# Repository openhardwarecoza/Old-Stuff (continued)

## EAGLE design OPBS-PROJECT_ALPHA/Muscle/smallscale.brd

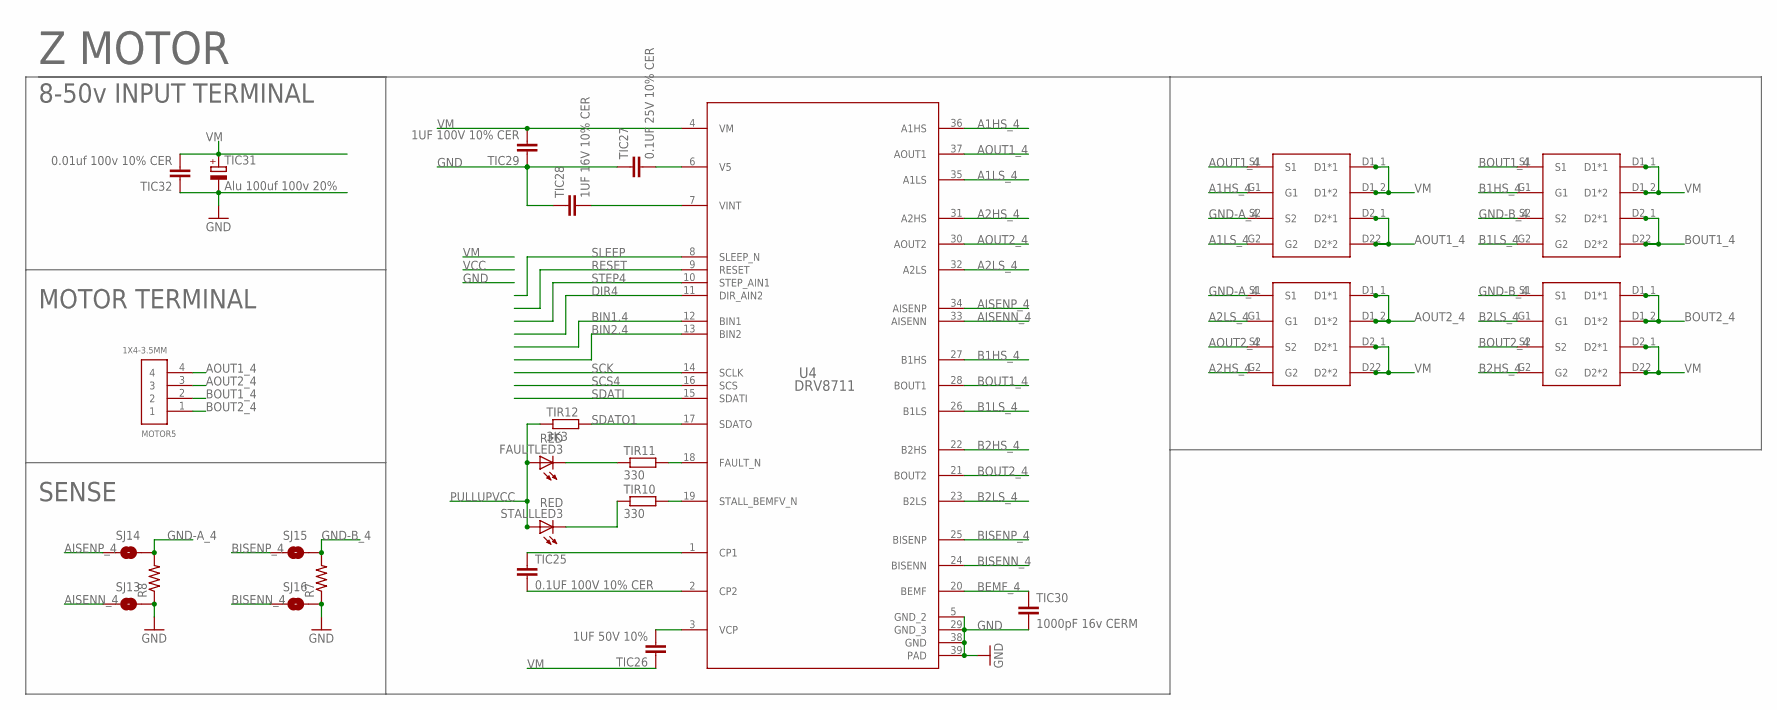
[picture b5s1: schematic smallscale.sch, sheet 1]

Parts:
FAULTLED3: RED; 1206
MOTOR5: 1X4-3.5MM; 1X04-3.5MM
R7, R8: R-US_R2512; R2512
SJ13, SJ14, SJ15, SJ16: SOLDERJUMPERTRACE; SJ_2S-TRACE
STALLLED3: RED; 1206
TIC25: 0.1UF 100V 10% CER; C0603K
TIC26: 1UF 50V 10%; C0805K
TIC27: 0.1UF 25V 10% CER; C0603K
TIC28: 1UF 16V 10% CER; C0603K
TIC29: 1UF 100V 10% CER; C1206K
TIC30: 1000pF 16v CERM; C0603K
TIC31: Alu 100uf 100v 20%; E5-10,5
TIC32: 0.01uf 100v 10% CER; C0603K
TIR10, TIR11: 330; R1206
TIR12: 3K3; R1206
U4: DRV8711; DCP0038A_N
U$13, U$14, U$15, U$16: CSD88537ND

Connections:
A1HS_4: U4.36 (A1HS), U$13.G1
A1LS_4: U4.35 (A1LS), U$13.G2
A2HS_4: U4.31 (A2HS), U$15.G2
A2LS_4: U4.32 (A2LS), U$15.G1
AISENN_4: SJ13.1, U4.33 (AISENN)
AISENP_4: SJ14.1, U4.34 (AISENP)
AOUT1_4: MOTOR5.4, U4.37 (AOUT1), U$13.D2_1 (D2*1), U$13.D22 (D2*2), U$13.S1
AOUT2_4: MOTOR5.3, U4.30 (AOUT2), U$15.D1_1 (D1*1), U$15.D1_2 (D1*2), U$15.S2
B1HS_4: U4.27 (B1HS), U$14.G1
B1LS_4: U4.26 (B1LS), U$14.G2
B2HS_4: U4.22 (B2HS), U$16.G2
B2LS_4: U4.23 (B2LS), U$16.G1
BEMF_4: TIC30.1, U4.20 (BEMF)
BIN1.4: U4.12 (BIN1)
BIN2.4: U4.13 (BIN2)
BISENN_4: SJ16.1, U4.24 (BISENN)
BISENP_4: SJ15.1, U4.25 (BISENP)
BOUT1_4: MOTOR5.2, U4.28 (BOUT1), U$14.D2_1 (D2*1), U$14.D22 (D2*2), U$14.S1
BOUT2_4: MOTOR5.1, U4.21 (BOUT2), U$16.D1_1 (D1*1), U$16.D1_2 (D1*2), U$16.S2
CP1_4: TIC25.1, U4.1 (CP1)
CP2_4: TIC25.2, U4.2 (CP2)
DIR4: U4.11 (DIR_AIN2)
FAULTLED4: FAULTLED3.C, TIR11.1
FAULT_N4: TIR11.2, U4.18 (FAULT_N)
GND: R7.1, R8.1, SJ13.2, SJ16.2, TIC27.1, TIC28.1, TIC29.1, TIC30.2, TIC31.-, TIC32.1, U4.5 (GND_2), U4.29 (GND_3), U4.38 (GND), U4.39 (PAD); also elsewhere on the board
GND-A_4: R8.2, SJ14.2, U$13.S2, U$15.S1
GND-B_4: R7.2, SJ15.2, U$14.S2, U$16.S1
PULLUPVCC: FAULTLED3.A, STALLLED3.A, TIR12.1
RESET: U4.9 (RESET)
SCK: U4.14 (SCLK)
SCS4: U4.16 (SCS)
SDATI: U4.15 (SDATI)
SDATO1: TIR12.2, U4.17 (SDATO)
SLEEP: U4.8 (SLEEP_N)
STALLLED4: STALLLED3.C, TIR10.1
STALL_N4: TIR10.2, U4.19 (STALL_BEMFV_N)
STEP4: U4.10 (STEP_AIN1)
V5_4: TIC27.2, U4.6 (V5)
VCP4: TIC26.2, U4.3 (VCP)
VINT4: TIC28.2, U4.7 (VINT)
VM: TIC26.1, TIC29.2, TIC31.+, TIC32.2, U4.4 (VM), U$13.D1_1 (D1*1), U$13.D1_2 (D1*2), U$14.D1_1 (D1*1), U$14.D1_2 (D1*2), U$15.D2_1 (D2*1), U$15.D22 (D2*2), U$16.D2_1 (D2*1), U$16.D22 (D2*2); also elsewhere on the board

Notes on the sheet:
8-50v INPUT TERMINAL
MOTOR TERMINAL
SENSE
Z MOTOR

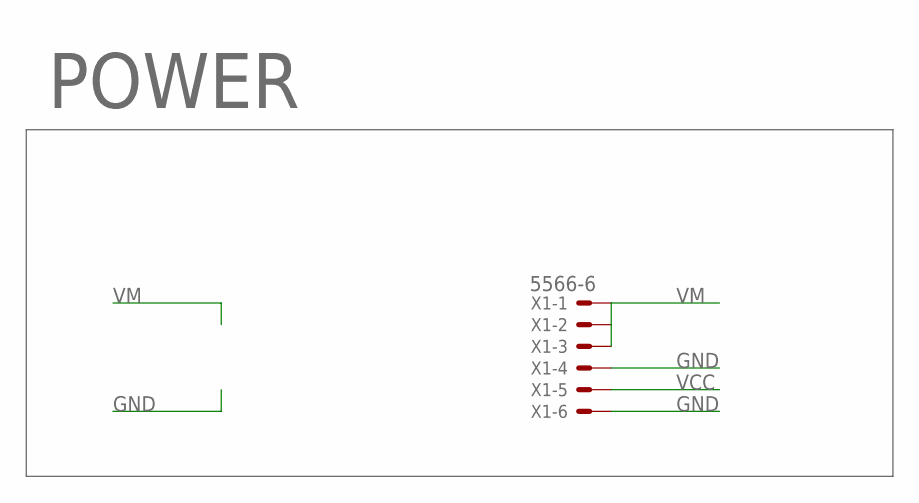
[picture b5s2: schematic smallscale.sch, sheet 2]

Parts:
X1: 5566-6

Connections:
GND: X1.4, X1.6; also elsewhere on the board
VCC: X1.5
VM: X1.1, X1.2, X1.3; also elsewhere on the board

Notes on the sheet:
POWER

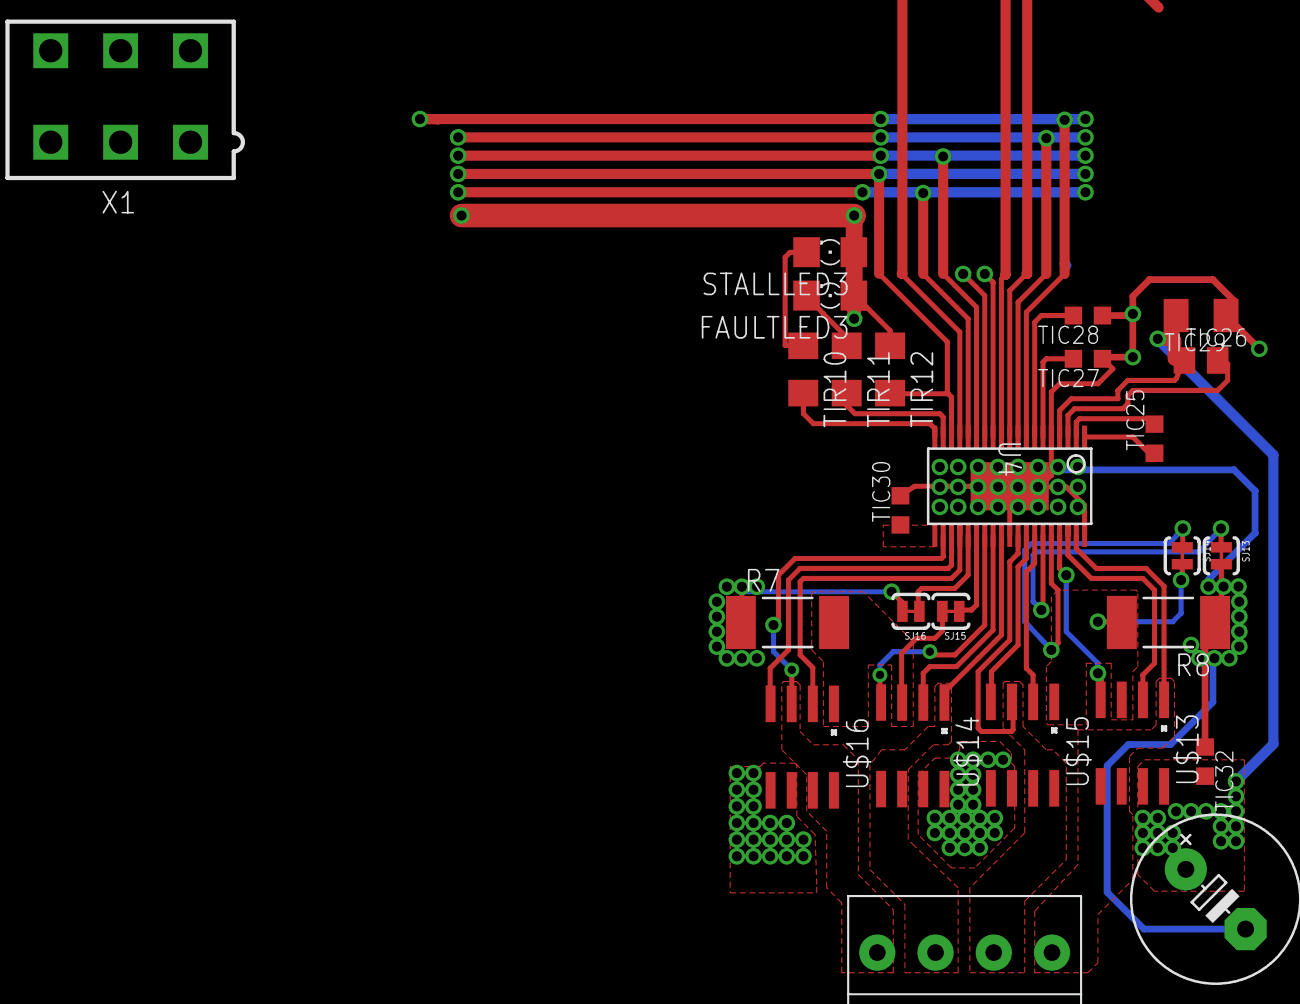
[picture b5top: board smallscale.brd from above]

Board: 2 copper layers, 26 parts (0 on the bottom side), 32 nets.

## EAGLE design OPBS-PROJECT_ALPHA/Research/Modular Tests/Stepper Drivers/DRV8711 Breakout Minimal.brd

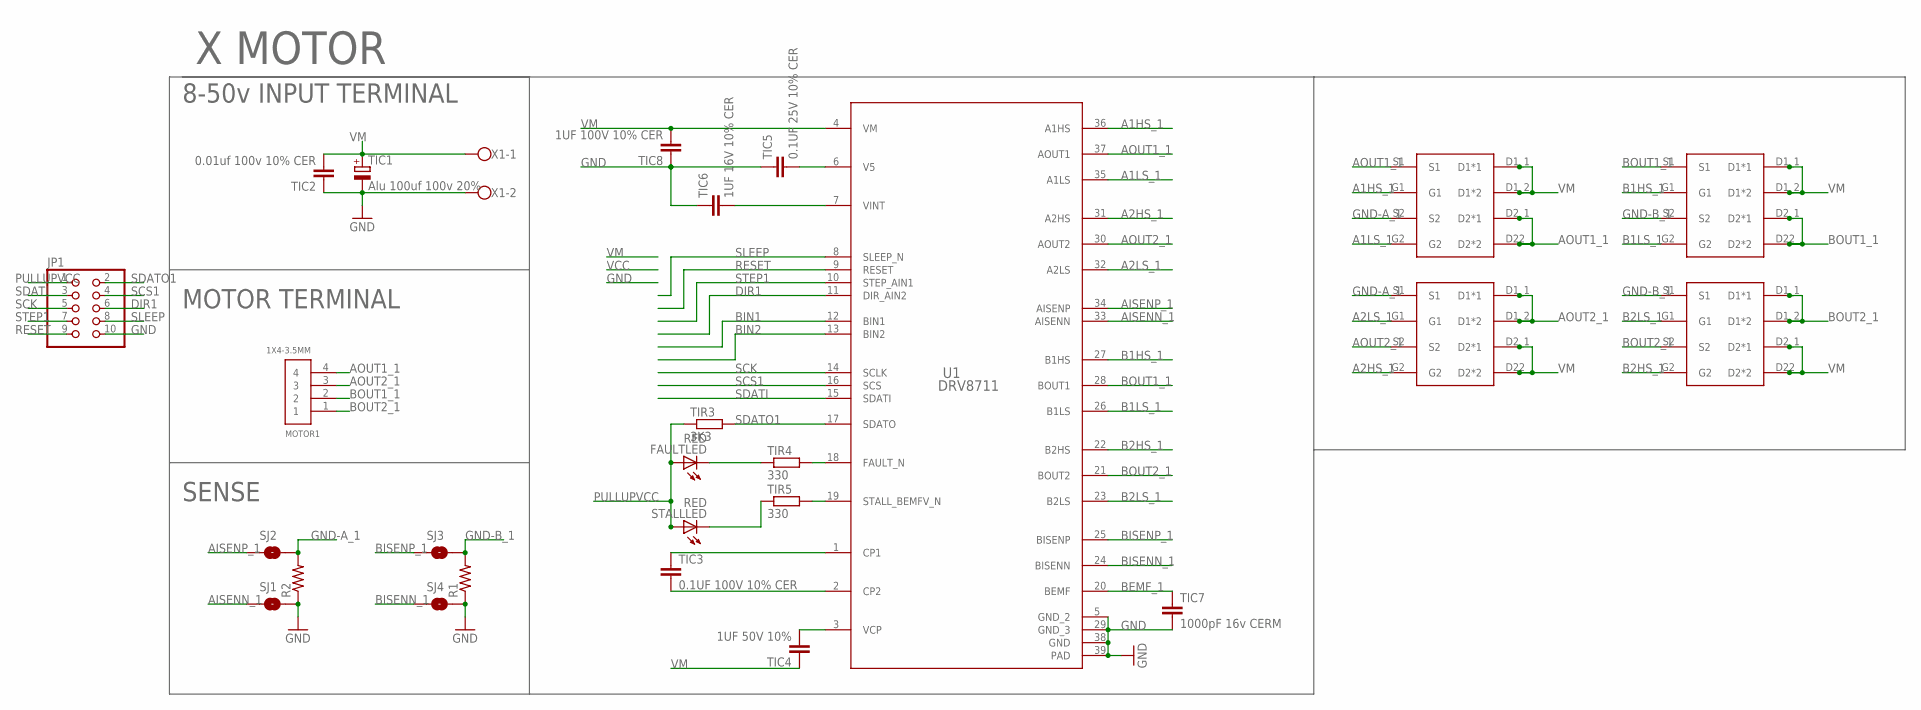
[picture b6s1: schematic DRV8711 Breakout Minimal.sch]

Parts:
FAULTLED: RED; 1206
JP1: PINHD-2X5; 2X05
MOTOR1: 1X4-3.5MM; 1X04-3.5MM
R1, R2: R-US_R2512; R2512
SJ1, SJ2, SJ3, SJ4: SOLDERJUMPERTRACE; SJ_2S-TRACE
STALLLED: RED; 1206
TIC1: Alu 100uf 100v 20%; PANASONIC_E
TIC2: 0.01uf 100v 10% CER; C1206K
TIC3: 0.1UF 100V 10% CER; C1206K
TIC4: 1UF 50V 10%; C1206K
TIC5: 0.1UF 25V 10% CER; C1206K
TIC6: 1UF 16V 10% CER; C1206K
TIC7: 1000pF 16v CERM; C1206K
TIC8: 1UF 100V 10% CER; C1206K
TIR3: 3K3; R1206
TIR4, TIR5: 330; R1206
U1: DRV8711; DCP0038A_N
U$1, U$2, U$3, U$4: CSD88537ND
X1: W237-102

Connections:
A1HS_1: U1.36 (A1HS), U$1.G1
A1LS_1: U1.35 (A1LS), U$1.G2
A2HS_1: U1.31 (A2HS), U$3.G2
A2LS_1: U1.32 (A2LS), U$3.G1
AISENN_1: SJ1.1, U1.33 (AISENN)
AISENP_1: SJ2.1, U1.34 (AISENP)
AOUT1_1: MOTOR1.4, U1.37 (AOUT1), U$1.D2_1 (D2*1), U$1.D22 (D2*2), U$1.S1
AOUT2_1: MOTOR1.3, U1.30 (AOUT2), U$3.D1_1 (D1*1), U$3.D1_2 (D1*2), U$3.S2
B1HS_1: U1.27 (B1HS), U$2.G1
B1LS_1: U1.26 (B1LS), U$2.G2
B2HS_1: U1.22 (B2HS), U$4.G2
B2LS_1: U1.23 (B2LS), U$4.G1
BEMF_1: TIC7.1, U1.20 (BEMF)
BIN1: U1.12 (BIN1)
BIN2: U1.13 (BIN2)
BISENN_1: SJ4.1, U1.24 (BISENN)
BISENP_1: SJ3.1, U1.25 (BISENP)
BOUT1_1: MOTOR1.2, U1.28 (BOUT1), U$2.D2_1 (D2*1), U$2.D22 (D2*2), U$2.S1
BOUT2_1: MOTOR1.1, U1.21 (BOUT2), U$4.D1_1 (D1*1), U$4.D1_2 (D1*2), U$4.S2
CP1_1: TIC3.1, U1.1 (CP1)
CP2_1: TIC3.2, U1.2 (CP2)
DIR1: JP1.6, U1.11 (DIR_AIN2)
FAULTLED: FAULTLED.C, TIR4.1
FAULT_N1: TIR4.2, U1.18 (FAULT_N)
GND: JP1.10, R1.1, R2.1, SJ1.2, SJ4.2, TIC1.-, TIC2.1, TIC5.1, TIC6.1, TIC7.2, TIC8.1, U1.5 (GND_2), U1.29 (GND_3), U1.38 (GND), U1.39 (PAD), X1.2
GND-A_1: R2.2, SJ2.2, U$1.S2, U$3.S1
GND-B_1: R1.2, SJ3.2, U$2.S2, U$4.S1
PULLUPVCC: FAULTLED.A, JP1.1, STALLLED.A, TIR3.1
RESET: JP1.9, U1.9 (RESET)
SCK: JP1.5, U1.14 (SCLK)
SCS1: JP1.4, U1.16 (SCS)
SDATI: JP1.3, U1.15 (SDATI)
SDATO1: JP1.2, TIR3.2, U1.17 (SDATO)
SLEEP: JP1.8, U1.8 (SLEEP_N)
STALLLED: STALLLED.C, TIR5.1
STALL_N1: TIR5.2, U1.19 (STALL_BEMFV_N)
STEP1: JP1.7, U1.10 (STEP_AIN1)
V5_1: TIC5.2, U1.6 (V5)
VCP1: TIC4.2, U1.3 (VCP)
VINT1: TIC6.2, U1.7 (VINT)
VM: TIC1.+, TIC2.2, TIC4.1, TIC8.2, U1.4 (VM), U$1.D1_1 (D1*1), U$1.D1_2 (D1*2), U$2.D1_1 (D1*1), U$2.D1_2 (D1*2), U$3.D2_1 (D2*1), U$3.D22 (D2*2), U$4.D2_1 (D2*1), U$4.D22 (D2*2), X1.1

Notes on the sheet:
8-50v INPUT TERMINAL
MOTOR TERMINAL
SENSE
X MOTOR

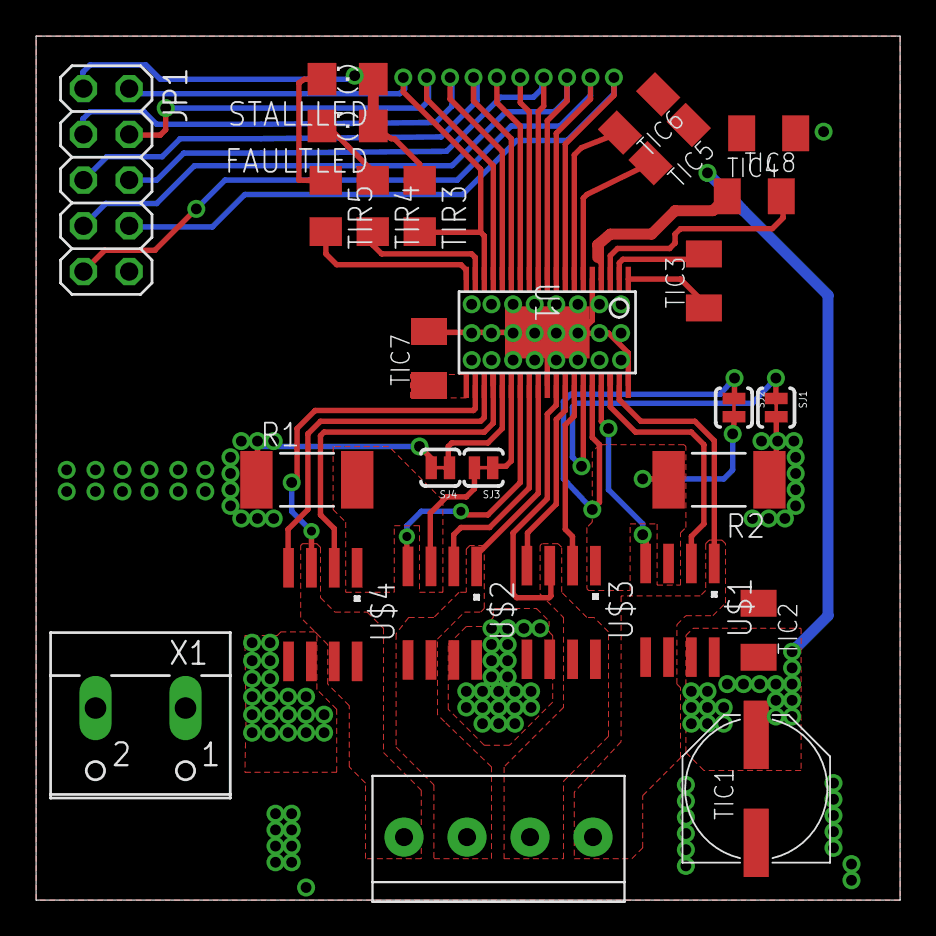
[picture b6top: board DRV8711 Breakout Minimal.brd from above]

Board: 2 copper layers, 48.0 x 48.0 mm, 27 parts (0 on the bottom side), 39 nets.

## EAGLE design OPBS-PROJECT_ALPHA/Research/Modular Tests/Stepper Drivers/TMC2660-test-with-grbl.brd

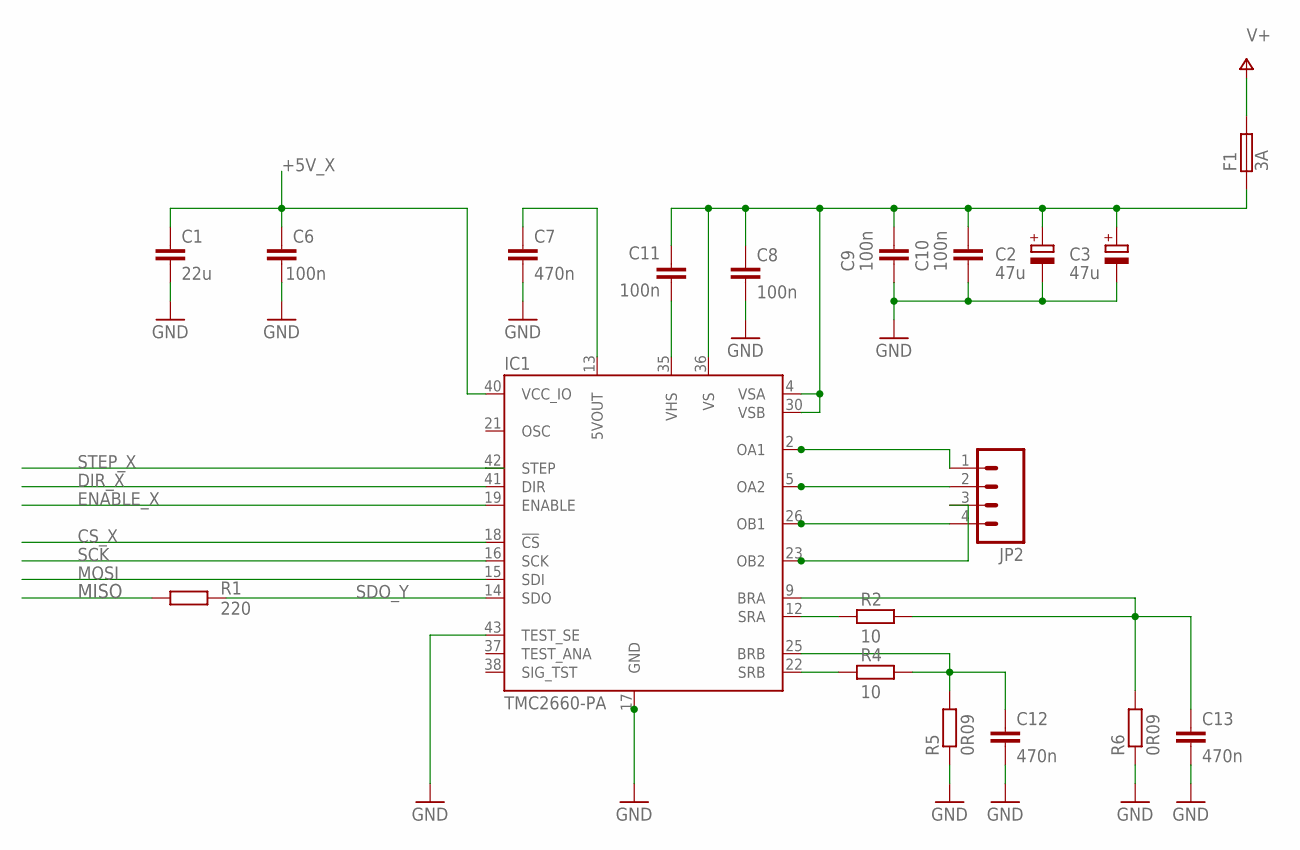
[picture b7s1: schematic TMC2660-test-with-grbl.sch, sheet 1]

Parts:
C1: 22u; C1206; VOLTAGE 6.3V; PARTNR JMK316B7226ML-T
C2, C3: 47u; E5-8,5; VOLTAGE 50V; PARTNR EEEFK1H470XP
C6: 100n; C1206K; VOLTAGE 25V; PARTNR C0603C104K3RACTU
C7, C12, C13: 470n; 0805-WIDE; VOLTAGE 10V; PARTNR VJ0805Y474KXQTW1BC
C8, C9, C10, C11: 100n; C0603K; VOLTAGE 50V; PARTNR C0603C104K5RACTU
F1: 3A; AF2; VOLTAGE 125V; PARTNR CB61F3A-TR2
IC1: TMC2660-PA; PQFP44; PARTNR TMC2660
JP2: M04SCREW; SCREWTERMINAL-3.5MM-4
R1: 220; R0603; PARTNR SG73S1JTTD221J
R2, R4: 10; R0603; PARTNR RN73H1JTTD10R0F100
R5, R6: 0R09; R2512; PARTNR ERJ-B2CFR091V

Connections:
+5V_X: C1.1, C6.2, IC1.40 (VCC_IO)
CS_X: IC1.18 (!CS); also elsewhere on the board
DIR_X: IC1.41 (DIR); also elsewhere on the board
ENABLE_X: IC1.19 (ENABLE); also elsewhere on the board
GND: C1.2, C2.-, C3.-, C6.1, C7.2, C8.2, C9.1, C10.1, C12.2, C13.2, IC1.17 (GND), IC1.39 (GND1), IC1.43 (TEST_SE), IC1.44 (GND2), R5.1, R6.1; also elsewhere on the board
MISO: R1.2; also elsewhere on the board
MOSI: IC1.15 (SDI); also elsewhere on the board
unnamed: IC1.22 (SRB), R4.2
unnamed: C12.1, IC1.25 (BRB), R4.1, R5.2
unnamed: C13.1, IC1.9 (BRA), R2.1, R6.2
unnamed: IC1.12 (SRA), R2.2
OA1: IC1.2 (OA1), IC1.3 (OA1_1), IC1.7 (OA1_2), IC1.8 (OA1_3), JP2.1
OA2: IC1.5 (OA2), IC1.6 (OA2_1), IC1.10 (OA2_2), IC1.11 (OA2_3), JP2.2
OB1: IC1.26 (OB1), IC1.27 (OB1_1), IC1.31 (OB1_2), IC1.32 (OB1_3), JP2.4
OB2: IC1.23 (OB2), IC1.24 (OB2_1), IC1.28 (OB2_2), IC1.29 (OB2_3), JP2.3
PWR_X: C2.+, C3.+, C8.1, C9.2, C10.2, C11.2, F1.P$1 (1), IC1.4 (VSA), IC1.30 (VSB), IC1.36 (VS)
SCK: IC1.16 (SCK); also elsewhere on the board
SDO_Y: IC1.14 (SDO), R1.1
STEP_X: IC1.42 (STEP); also elsewhere on the board
V+: F1.P$2 (2); also elsewhere on the board
VHS: C11.1, IC1.35 (VHS)
VREG: C7.1, IC1.13 (5VOUT)

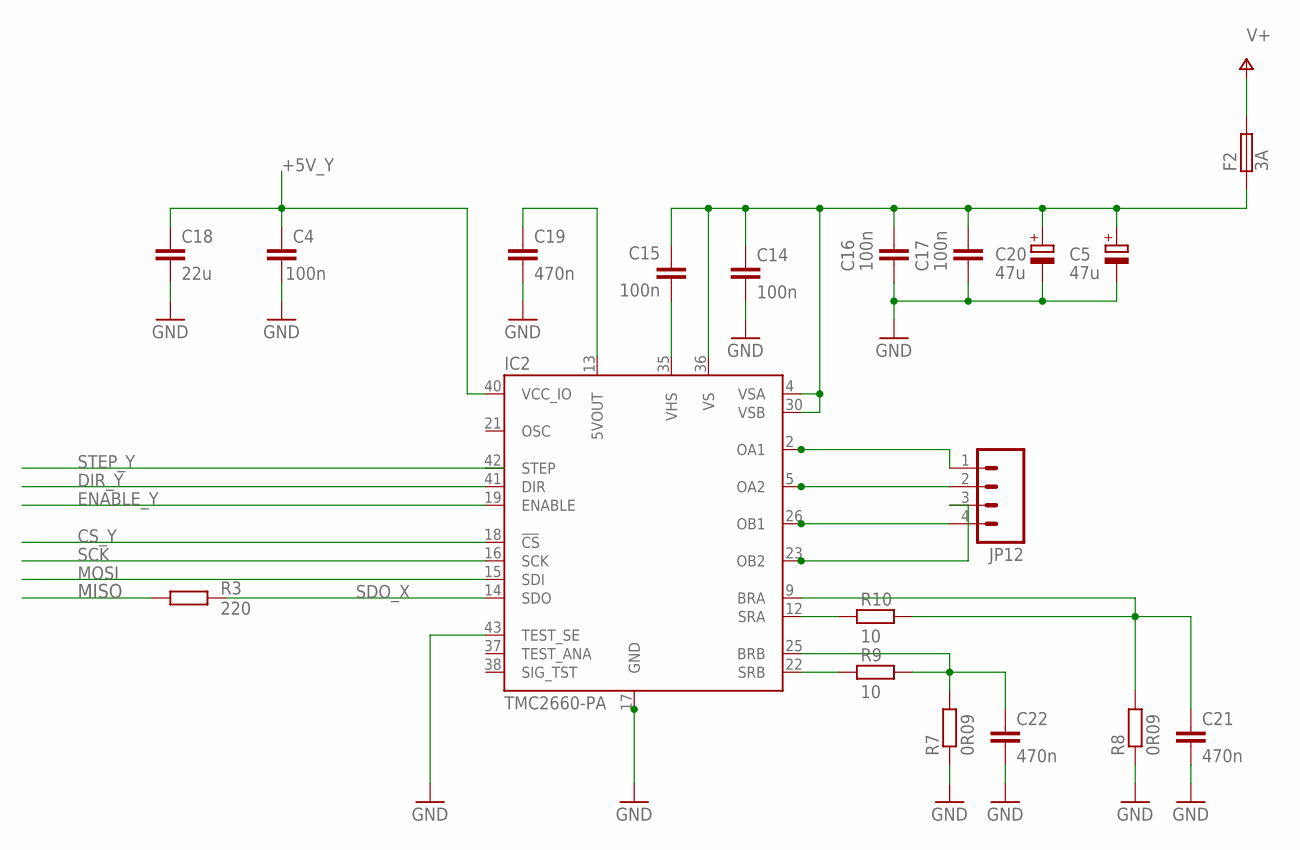
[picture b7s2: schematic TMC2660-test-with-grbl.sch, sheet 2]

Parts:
C4: 100n; C1206K; VOLTAGE 25V; PARTNR C0603C104K3RACTU
C5, C20: 47u; E5-8,5; VOLTAGE 50V; PARTNR EEEFK1H470XP
C14, C15, C16, C17: 100n; C0603K; VOLTAGE 50V; PARTNR C0603C104K5RACTU
C18: 22u; C1206; VOLTAGE 6.3V; PARTNR JMK316B7226ML-T
C19, C21, C22: 470n; 0805-WIDE; VOLTAGE 10V; PARTNR VJ0805Y474KXQTW1BC
F2: 3A; AF2; VOLTAGE 125V; PARTNR CB61F3A-TR2
IC2: TMC2660-PA; PQFP44; PARTNR TMC2660
JP12: M04SCREW; SCREWTERMINAL-3.5MM-4
R3: 220; R0603; PARTNR SG73S1JTTD221J
R7, R8: 0R09; R2512; PARTNR ERJ-B2CFR091V
R9, R10: 10; R0603; PARTNR RN73H1JTTD10R0F100

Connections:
+5V_Y: C4.2, C18.1, IC2.40 (VCC_IO)
CS_Y: IC2.18 (!CS); also elsewhere on the board
DIR_Y: IC2.41 (DIR); also elsewhere on the board
ENABLE_Y: IC2.19 (ENABLE); also elsewhere on the board
GND: C4.1, C5.-, C14.2, C16.1, C17.1, C18.2, C19.2, C20.-, C21.2, C22.2, IC2.17 (GND), IC2.39 (GND1), IC2.43 (TEST_SE), IC2.44 (GND2), R7.1, R8.1; also elsewhere on the board
MISO: R3.2; also elsewhere on the board
MOSI: IC2.15 (SDI); also elsewhere on the board
unnamed: C22.1, IC2.25 (BRB), R7.2, R9.1
unnamed: C21.1, IC2.9 (BRA), R8.2, R10.1
unnamed: IC2.22 (SRB), R9.2
unnamed: IC2.12 (SRA), R10.2
OA3: IC2.2 (OA1), IC2.3 (OA1_1), IC2.7 (OA1_2), IC2.8 (OA1_3), JP12.1
OA4: IC2.5 (OA2), IC2.6 (OA2_1), IC2.10 (OA2_2), IC2.11 (OA2_3), JP12.2
OB3: IC2.23 (OB2), IC2.24 (OB2_1), IC2.28 (OB2_2), IC2.29 (OB2_3), JP12.3
OB4: IC2.26 (OB1), IC2.27 (OB1_1), IC2.31 (OB1_2), IC2.32 (OB1_3), JP12.4
PWR_Y: C5.+, C14.1, C15.2, C16.2, C17.2, C20.+, F2.P$1 (1), IC2.4 (VSA), IC2.30 (VSB), IC2.36 (VS)
SCK: IC2.16 (SCK); also elsewhere on the board
SDO_X: IC2.14 (SDO), R3.1
STEP_Y: IC2.42 (STEP); also elsewhere on the board
V+: F2.P$2 (2); also elsewhere on the board
VHS1: C15.1, IC2.35 (VHS)
VREG1: C19.1, IC2.13 (5VOUT)

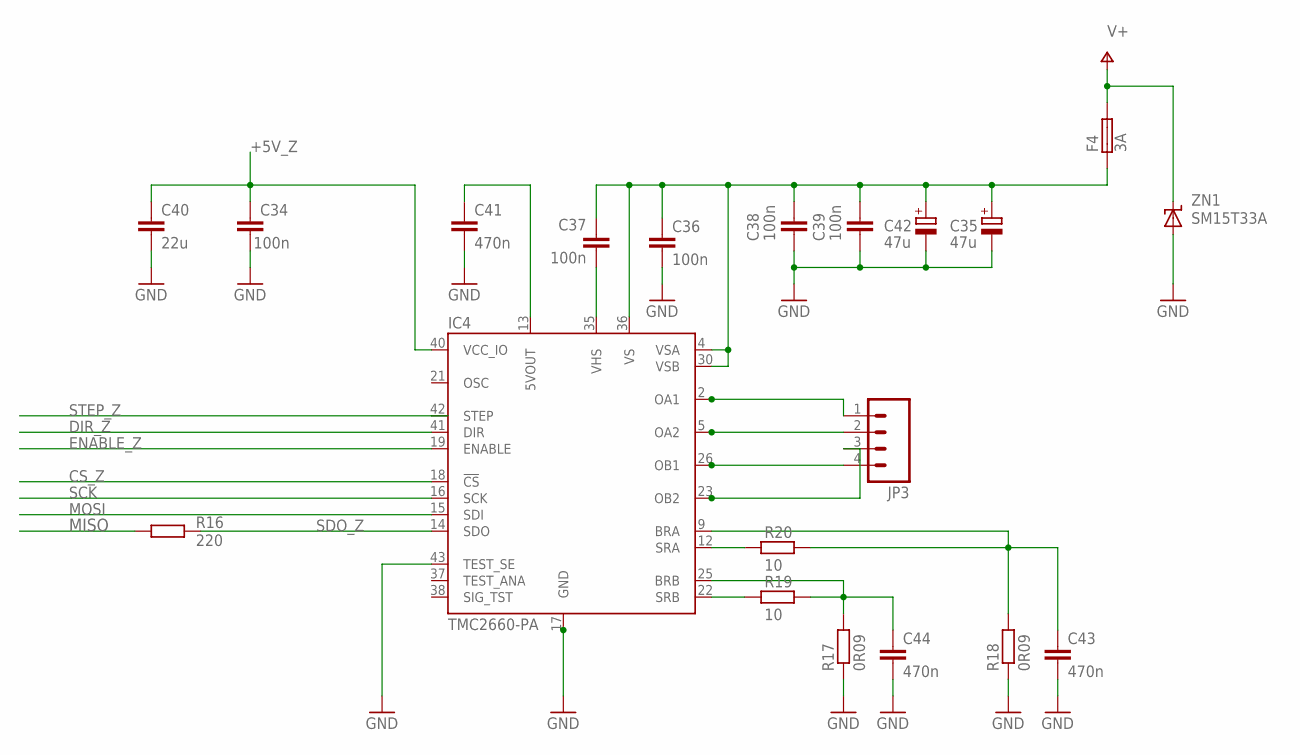
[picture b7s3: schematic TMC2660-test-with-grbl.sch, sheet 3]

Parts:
C34: 100n; C1206K; VOLTAGE 25V; PARTNR C0603C104K3RACTU
C35, C42: 47u; E5-8,5; VOLTAGE 50V; PARTNR EEEFK1H470XP
C36, C37, C38, C39: 100n; C0603K; VOLTAGE 50V; PARTNR C0603C104K5RACTU
C40: 22u; C1206; VOLTAGE 6.3V; PARTNR JMK316B7226ML-T
C41, C43, C44: 470n; 0805-WIDE; VOLTAGE 10V; PARTNR VJ0805Y474KXQTW1BC
F4: 3A; AF2; VOLTAGE 125V; PARTNR CB61F3A-TR2
IC4: TMC2660-PA; PQFP44; PARTNR TMC2660
JP3: M04SCREW; SCREWTERMINAL-3.5MM-4
R16: 220; R0603; PARTNR SG73S1JTTD221J
R17, R18: 0R09; R2512; PARTNR ERJ-B2CFR091V
R19, R20: 10; R0603; PARTNR RN73H1JTTD10R0F100
ZN1: SM15T33A; SMC; PARTNR SM15T33A

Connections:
+5V_Z: C34.2, C40.1, IC4.40 (VCC_IO)
CS_Z: IC4.18 (!CS); also elsewhere on the board
DIR_Z: IC4.41 (DIR); also elsewhere on the board
ENABLE_Z: IC4.19 (ENABLE); also elsewhere on the board
GND: C34.1, C35.-, C36.2, C38.1, C39.1, C40.2, C41.2, C42.-, C43.2, C44.2, IC4.17 (GND), IC4.39 (GND1), IC4.43 (TEST_SE), IC4.44 (GND2), R17.1, R18.1, ZN1.P$2 (A); also elsewhere on the board
MISO: R16.2; also elsewhere on the board
MOSI: IC4.15 (SDI); also elsewhere on the board
unnamed: C44.1, IC4.25 (BRB), R17.2, R19.1
unnamed: C43.1, IC4.9 (BRA), R18.2, R20.1
unnamed: IC4.22 (SRB), R19.2
unnamed: IC4.12 (SRA), R20.2
OA5: IC4.2 (OA1), IC4.3 (OA1_1), IC4.7 (OA1_2), IC4.8 (OA1_3), JP3.1
OA6: IC4.5 (OA2), IC4.6 (OA2_1), IC4.10 (OA2_2), IC4.11 (OA2_3), JP3.2
OB5: IC4.23 (OB2), IC4.24 (OB2_1), IC4.28 (OB2_2), IC4.29 (OB2_3), JP3.3
OB6: IC4.26 (OB1), IC4.27 (OB1_1), IC4.31 (OB1_2), IC4.32 (OB1_3), JP3.4
PWR_Z: C35.+, C36.1, C37.2, C38.2, C39.2, C42.+, F4.P$1 (1), IC4.4 (VSA), IC4.30 (VSB), IC4.36 (VS)
SCK: IC4.16 (SCK); also elsewhere on the board
SDO_Z: IC4.14 (SDO), R16.1
STEP_Z: IC4.42 (STEP); also elsewhere on the board
V+: F4.P$2 (2), ZN1.P$1 (C); also elsewhere on the board
VHS2: C37.1, IC4.35 (VHS)
VREG2: C41.1, IC4.13 (5VOUT)

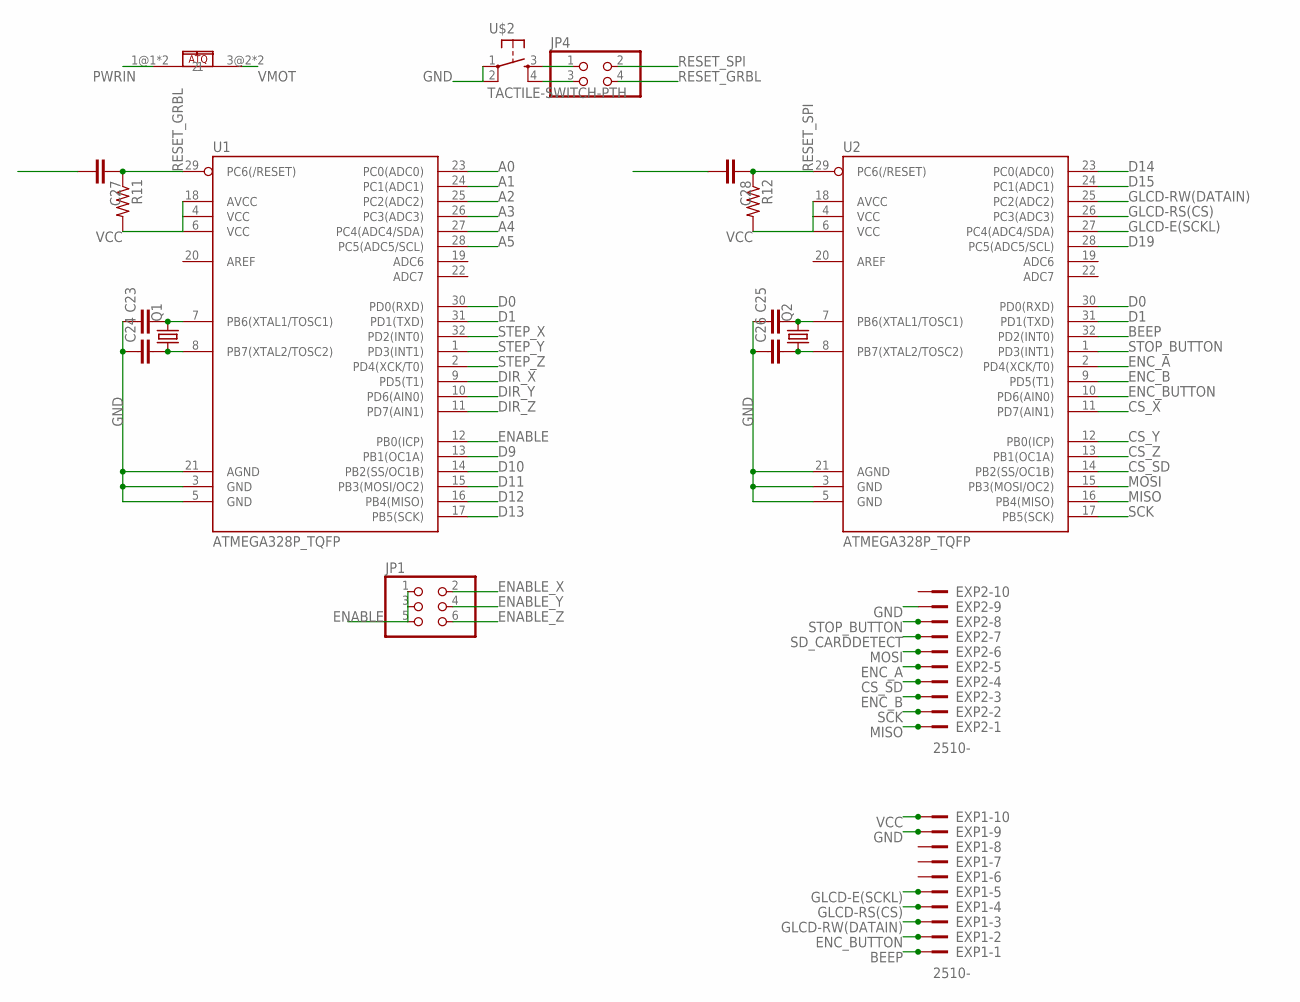
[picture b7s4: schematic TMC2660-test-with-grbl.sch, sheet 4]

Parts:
C23, C24, C25, C26, C27, C28: CAP1206; 1206
EXP1, EXP2: 2510-; PAK100/2500-10
JP1: PINHD-2X3; 2X03
JP4: PINHD-2X2; 2X02
Q1, Q2: CRYSTALHC49UP; HC49UP
R11, R12: RESISTOR1206; 1206
U1, U2: ATMEGA328P_TQFP; TQFP32-08
U$2: TACTILE-SWITCH-PTH; TAC-SWITCH-PTH
U$6: CQ-121; CQ121

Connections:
A0: U1.23 (PC0(ADC0))
A1: U1.24 (PC1(ADC1))
A2: U1.25 (PC2(ADC2))
A3: U1.26 (PC3(ADC3))
A4: U1.27 (PC4(ADC4/SDA))
A5: U1.28 (PC5(ADC5/SCL))
BEEP: EXP1.1, U2.32 (PD2(INT0))
CS_SD: EXP2.4, U2.14 (PB2(SS/OC1B))
CS_X: U2.11 (PD7(AIN1)); also elsewhere on the board
CS_Y: U2.12 (PB0(ICP)); also elsewhere on the board
CS_Z: U2.13 (PB1(OC1A)); also elsewhere on the board
D0: U1.30 (PD0(RXD)), U2.30 (PD0(RXD))
D1: U1.31 (PD1(TXD)), U2.31 (PD1(TXD))
D9: U1.13 (PB1(OC1A))
D10: U1.14 (PB2(SS/OC1B))
D11: U1.15 (PB3(MOSI/OC2))
D12: U1.16 (PB4(MISO))
D13: U1.17 (PB5(SCK))
D14: U2.23 (PC0(ADC0))
D15: U2.24 (PC1(ADC1))
D19: U2.28 (PC5(ADC5/SCL))
DIR_X: U1.9 (PD5(T1)); also elsewhere on the board
DIR_Y: U1.10 (PD6(AIN0)); also elsewhere on the board
DIR_Z: U1.11 (PD7(AIN1)); also elsewhere on the board
DTR_GRBL: C27.2
DTR_SPI: C28.2
ENABLE: JP1.1, JP1.3, JP1.5, U1.12 (PB0(ICP))
ENABLE_X: JP1.2; also elsewhere on the board
ENABLE_Y: JP1.4; also elsewhere on the board
ENABLE_Z: JP1.6; also elsewhere on the board
ENC_A: EXP2.5, U2.2 (PD4(XCK/T0))
ENC_B: EXP2.3, U2.9 (PD5(T1))
ENC_BUTTON: EXP1.2, U2.10 (PD6(AIN0))
GLCD-E(SCKL): EXP1.5, U2.27 (PC4(ADC4/SDA))
GLCD-RS(CS): EXP1.4, U2.26 (PC3(ADC3))
GLCD-RW(DATAIN): EXP1.3, U2.25 (PC2(ADC2))
GND: C23.1, C24.1, C25.1, C26.1, EXP1.9, EXP2.9, U1.3 (GND), U1.5 (GND), U1.21 (AGND), U2.3 (GND), U2.5 (GND), U2.21 (AGND), U$2.1, U$2.2; also elsewhere on the board
MISO: EXP2.1, U2.16 (PB4(MISO)); also elsewhere on the board
MOSI: EXP2.6, U2.15 (PB3(MOSI/OC2)); also elsewhere on the board
unnamed: C23.2, Q1.2, U1.7 (PB6(XTAL1/TOSC1))
unnamed: C24.2, Q1.1, U1.8 (PB7(XTAL2/TOSC2))
unnamed: C25.2, Q2.2, U2.7 (PB6(XTAL1/TOSC1))
unnamed: C26.2, Q2.1, U2.8 (PB7(XTAL2/TOSC2))
PWRIN: U$6.1@1 (1), U$6.2@1 (1)
RESET: JP4.1, JP4.3, U$2.3, U$2.4
RESET_GRBL: C27.1, JP4.4, R11.1, U1.29 (PC6(/RESET))
RESET_SPI: C28.1, JP4.2, R12.1, U2.29 (PC6(/RESET))
SCK: EXP2.2, U2.17 (PB5(SCK)); also elsewhere on the board
SD_CARDDETECT: EXP2.7
STEP_X: U1.32 (PD2(INT0)); also elsewhere on the board
STEP_Y: U1.1 (PD3(INT1)); also elsewhere on the board
STEP_Z: U1.2 (PD4(XCK/T0)); also elsewhere on the board
STOP_BUTTON: EXP2.8, U2.1 (PD3(INT1))
VCC: EXP1.10, R11.2, R12.2, U1.4 (VCC), U1.6 (VCC), U1.18 (AVCC), U2.4 (VCC), U2.6 (VCC), U2.18 (AVCC)
VMOT: U$6.3@2 (2), U$6.4@2 (2)

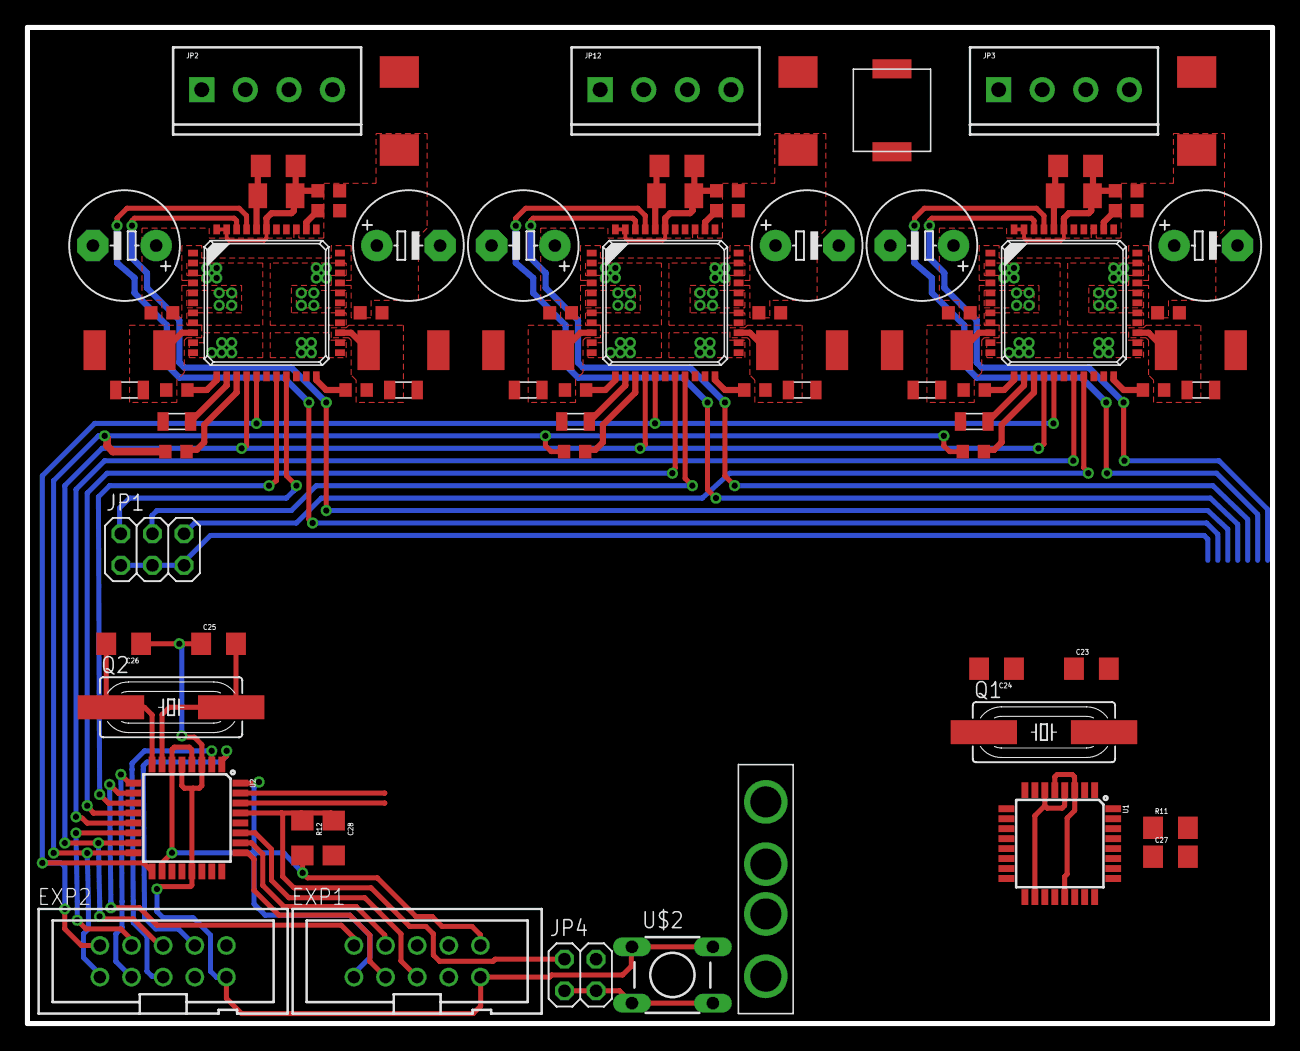
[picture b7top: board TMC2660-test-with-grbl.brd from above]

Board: 2 copper layers, 100.0 x 80.0 mm, 76 parts (0 on the bottom side), 78 nets.
